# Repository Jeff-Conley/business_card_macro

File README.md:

# business_card_macro
business card that can be used as a macropad
Created by Jeff Conley

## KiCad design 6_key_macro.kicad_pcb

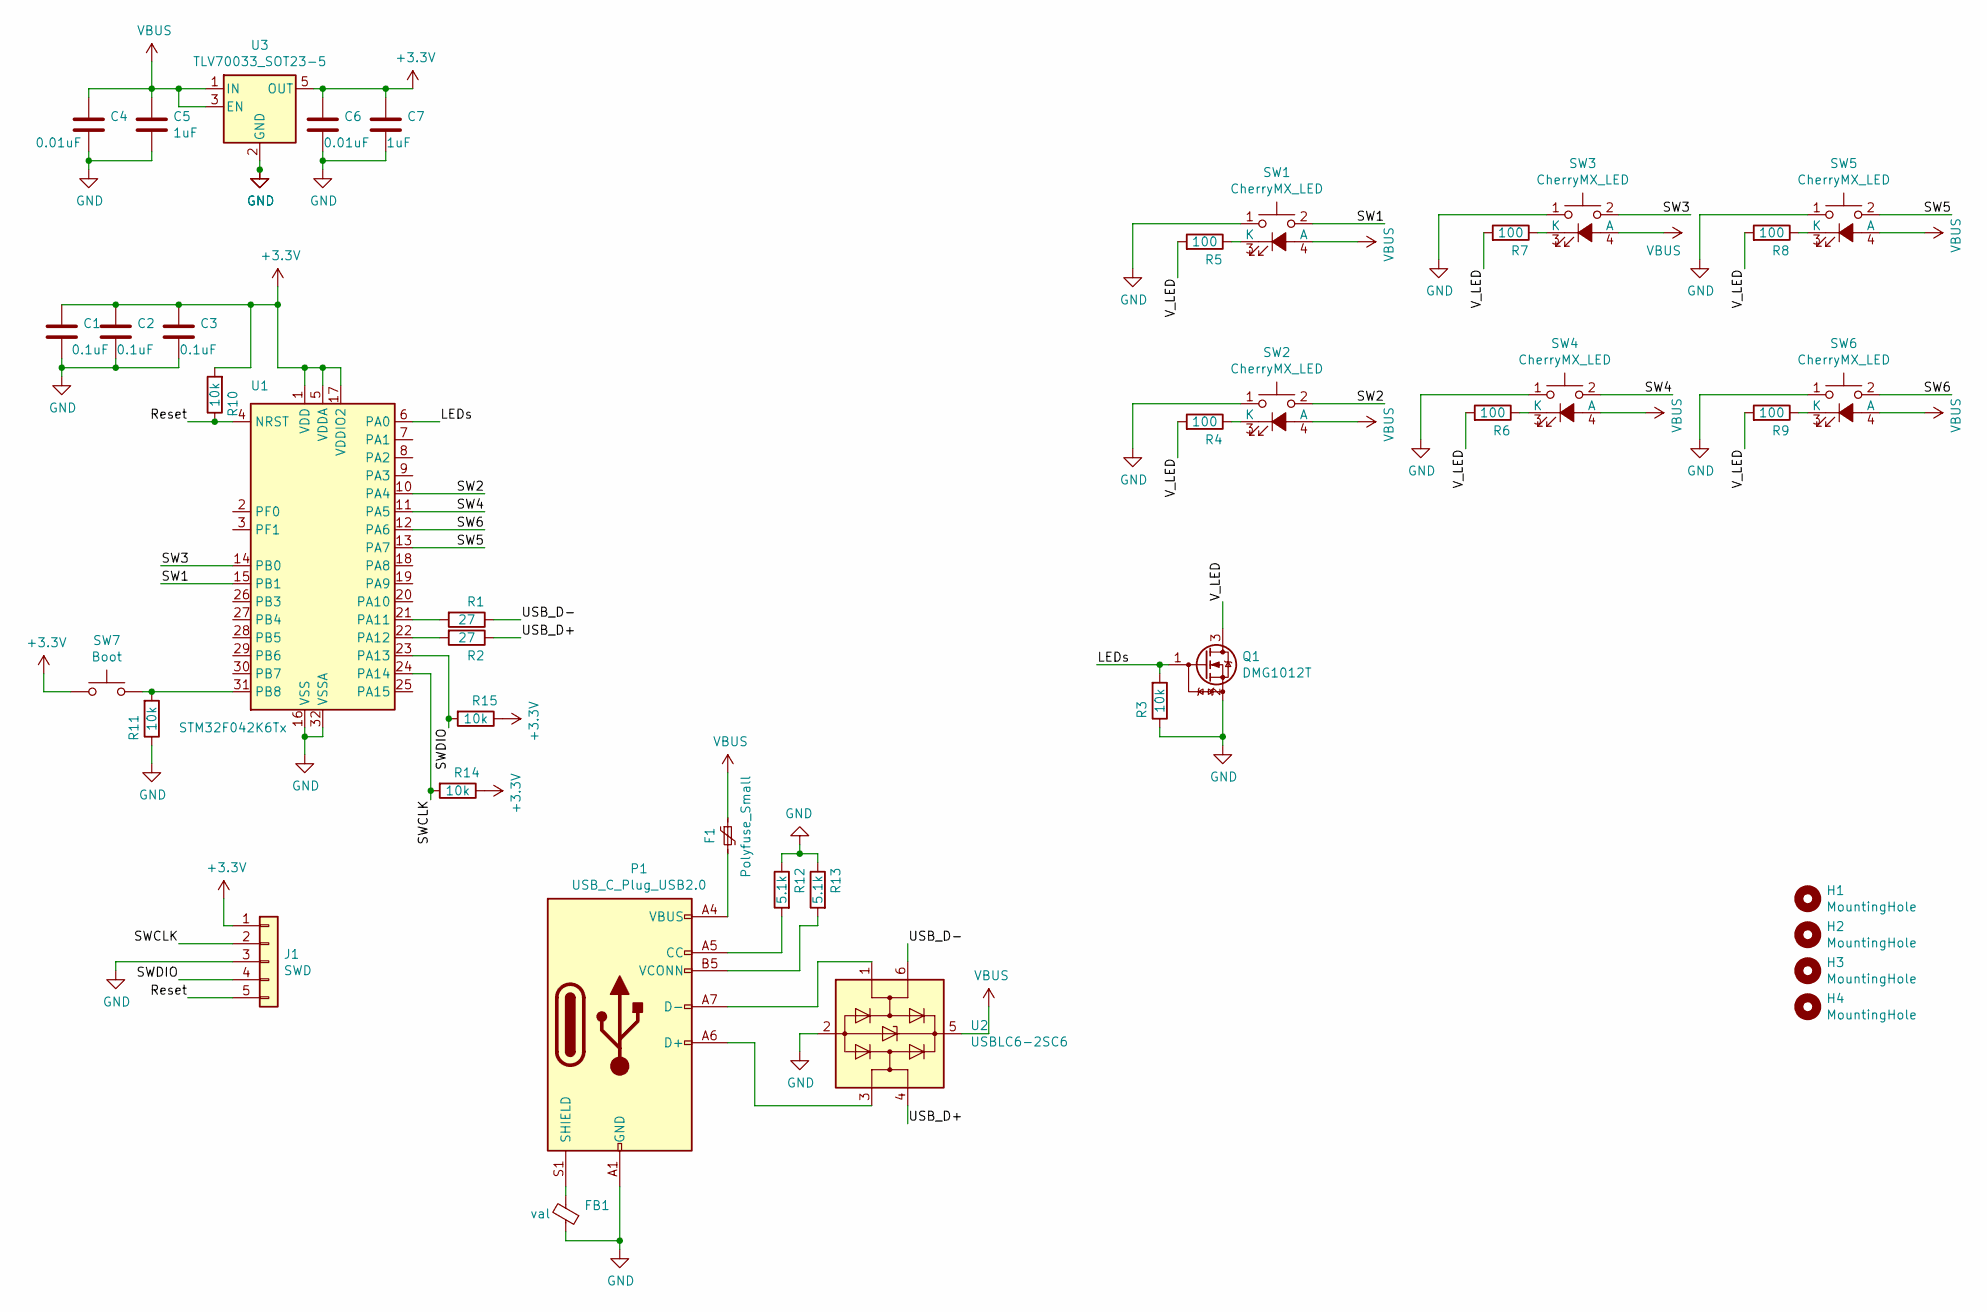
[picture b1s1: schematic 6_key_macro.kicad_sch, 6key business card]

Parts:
C1, C2, C3: 0.1uF; C_0805_2012Metric_Pad1.18x1.45mm_HandSolder
C4, C6: 0.01uF; C_0805_2012Metric_Pad1.18x1.45mm_HandSolder
C5, C7: 1uF; C_0805_2012Metric_Pad1.18x1.45mm_HandSolder
F1: Polyfuse_Small; Fuse_0805_2012Metric_Pad1.15x1.40mm_HandSolder
FB1: val; L_0805_2012Metric_Pad1.05x1.20mm_HandSolder
H1, H2, H3, H4: MountingHole; MountingHole_3.2mm_M3
J1: SWD; PinHeader_1x05_P2.54mm_Vertical
P1: USB_C_Plug_USB2.0; USB_C_Receptacle_Palconn_UTC16-G
Q1: DMG1012T; SOT-323_SC-70_Handsoldering
R1, R2: 27; R_0805_2012Metric_Pad1.20x1.40mm_HandSolder
R3, R10, R11, R14, R15: 10k; R_0805_2012Metric_Pad1.20x1.40mm_HandSolder
R4, R5, R6, R7, R8, R9: 100; R_0805_2012Metric_Pad1.20x1.40mm_HandSolder
R12, R13: 5.1k; R_0805_2012Metric_Pad1.20x1.40mm_HandSolder
SW1, SW2, SW3, SW4, SW5, SW6: CherryMX_LED; CherryMX_1.00u_PCB_LED
SW7: Boot; SW_PUSH_6mm
U1: STM32F042K6Tx; LQFP-32_7x7mm_P0.8mm
U2: USBLC6-2SC6; SOT-23-6
U3: TLV70033_SOT23-5; SOT-23-5

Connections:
+3V3: C1.1, C2.1, C3.1, C6.1, C7.1, J1.1, R10.2, R14.1, R15.1, SW7.1, U1.1 (VDD), U1.5 (VDDA), U1.17 (VDDIO2), U3.5 (OUT)
/LEDs: Q1.1 (G), R3.2, U1.6 (PA0)
/Reset: J1.5, R10.1, U1.4 (NRST)
/SW1: SW1.2, U1.15 (PB1)
/SW2: SW2.2, U1.10 (PA4)
/SW3: SW3.2, U1.14 (PB0)
/SW4: SW4.2, U1.11 (PA5)
/SW5: SW5.2, U1.13 (PA7)
/SW6: SW6.2, U1.12 (PA6)
/SWCLK: J1.2, R14.2, U1.24 (PA14)
/SWDIO: J1.4, R15.2, U1.23 (PA13)
/USB_D+: R2.1, U2.4 (I/O2)
/USB_D-: R1.1, U2.6 (I/O1)
/V_LED: Q1.3 (D), R4.2, R5.2, R6.2, R7.2, R8.2, R9.2
GND: C1.2, C2.2, C3.2, C4.2, C5.2, C6.2, C7.2, FB1.1, J1.3, P1.A1 (GND), P1.A12 (GND), P1.B1 (GND), P1.B12 (GND), Q1.2 (S), R3.1, R11.1, R12.1, R13.1, SW1.1, SW2.1, SW3.1, SW4.1, SW5.1, SW6.1, U1.16 (VSS), U1.32 (VSSA), U2.2 (GND), U3.2 (GND)
unnamed: F1.2, P1.A4 (VBUS), P1.A9 (VBUS), P1.B4 (VBUS), P1.B9 (VBUS)
unnamed: FB1.2, P1.S1 (SHIELD)
unnamed: P1.A5 (CC), R12.2
unnamed: P1.A6 (D+), U2.3 (I/O2)
unnamed: P1.A7 (D-), U2.1 (I/O1)
unnamed: P1.B5 (VCONN), R13.2
unnamed: R1.2, U1.21 (PA11)
unnamed: R2.2, U1.22 (PA12)
unnamed: R4.1, SW2.3 (K)
unnamed: R5.1, SW1.3 (K)
unnamed: R6.1, SW4.3 (K)
unnamed: R7.1, SW3.3 (K)
unnamed: R8.1, SW5.3 (K)
unnamed: R9.1, SW6.3 (K)
unnamed: R11.2, SW7.2, U1.31 (PB8)
VBUS: C4.1, C5.1, F1.1, SW1.4 (A), SW2.4 (A), SW3.4 (A), SW4.4 (A), SW5.4 (A), SW6.4 (A), U2.5 (VBUS), U3.1 (IN), U3.3 (EN)

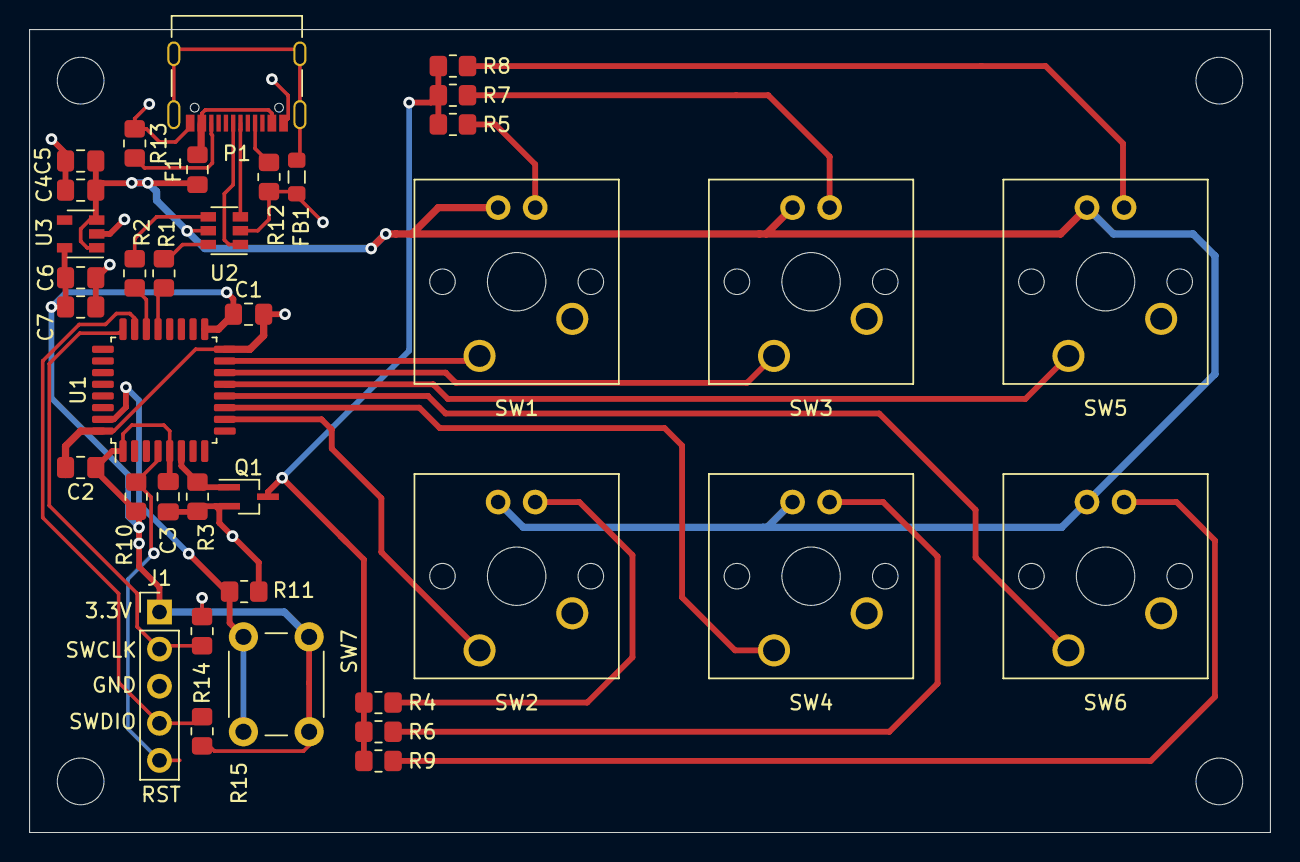
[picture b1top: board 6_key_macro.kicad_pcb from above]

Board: 2 copper layers, 85.0 x 55.0 mm, 41 parts (0 on the bottom side), 31 nets.

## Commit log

2021-10-24 version 0.2
2021-10-25 added 5.1k resistors to cc1 and cc2 for usb-c to usb-c compatibility
2021-10-26 swapped tvs diodes
2021-11-10 moved files to top level. Decided to move firmware to separate repo
2021-11-14 added files for 3d printed case
2021-12-31 update case design
2021-12-31 update files to kicad V6
